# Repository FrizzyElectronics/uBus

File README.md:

# uBus
Conversor USB-micro a Serial IC. 5V/3.3V compatible

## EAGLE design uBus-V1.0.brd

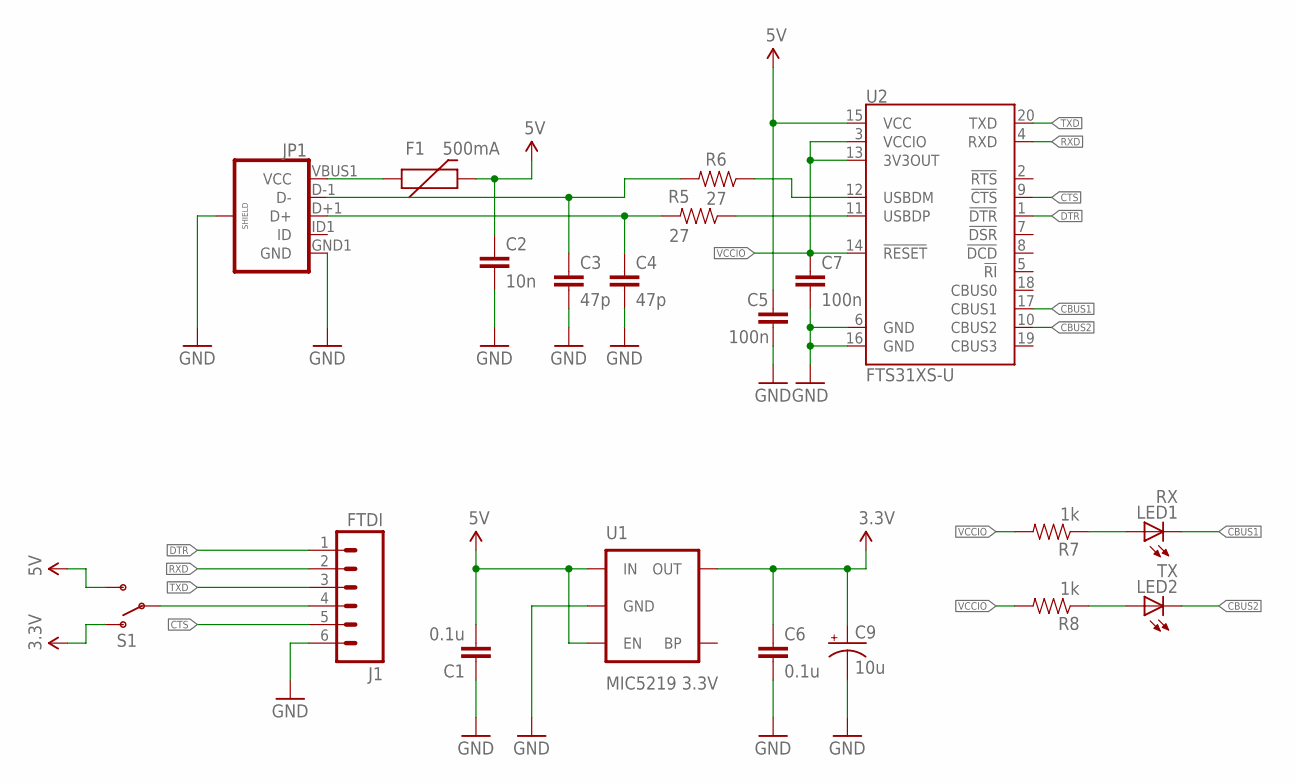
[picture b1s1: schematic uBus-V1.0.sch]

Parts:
C1, C6: 0.1u; 0603-CAP
C2: 10n; 0603-CAP
C3, C4: 47p; 0603-CAP
C5, C7: 100n; 0603-CAP
C9: 10u; SMC_P
F1: 500mA; PTC-1206
J1: FTDI; 1X06_LONGPADS
JP1: USB_MICROB_PLUGCONN-11752; USB-B-MICRO-SMD_V03
LED1: RX; CHIP-LED0603
LED2: TX; CHIP-LED0603
R5, R6: 27; 0603-RES
R7, R8: 1k; 0603-RES
S1: SWITCH-SPDT-SMD-A; SWITCH-SPST-SMD-A
U1: MIC5219 3.3V; SOT23-5
U2: FTS31XS-U; SSOP20_L

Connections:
3.3V: C6.1, C9.+, S1.1 (O), U1.5 (OUT)
5V: C1.2, C2.1, C5.1, F1.2, S1.3 (S), U1.1 (IN), U1.3 (EN), U2.15 (VCC)
CBUS1: LED1.C, U2.17 (CBUS1)
CBUS2: LED2.C, U2.10 (CBUS2)
CTS: J1.5, U2.9 (!CTS)
DTR: J1.1, U2.1 (!DTR)
GND: C1.1, C2.2, C3.2, C4.2, C5.2, C6.2, C7.2, C9.-, J1.6, JP1.GND1 (GND), JP1.SHIELD1 (SHIELD), JP1.SHIELD2 (SHIELD), JP1.SHIELD3 (SHIELD), U1.2 (GND), U2.6 (GND), U2.16 (GND)
unnamed: J1.4, S1.2
unnamed: LED2.A, R8.1
unnamed: LED1.A, R7.1
unnamed: R6.1, U2.12 (USBDM)
unnamed: R5.1, U2.11 (USBDP)
unnamed: C4.1, JP1.D+1 (D+), R5.2
unnamed: C3.1, JP1.D-1 (D-), R6.2
unnamed: F1.1, JP1.VBUS1 (VCC)
RXD: J1.2, U2.4 (RXD)
TXD: J1.3, U2.20 (TXD)
VCCIO: C7.1, R7.2, R8.2, U2.3 (VCCIO), U2.13 (3V3OUT), U2.14 (!RESET)

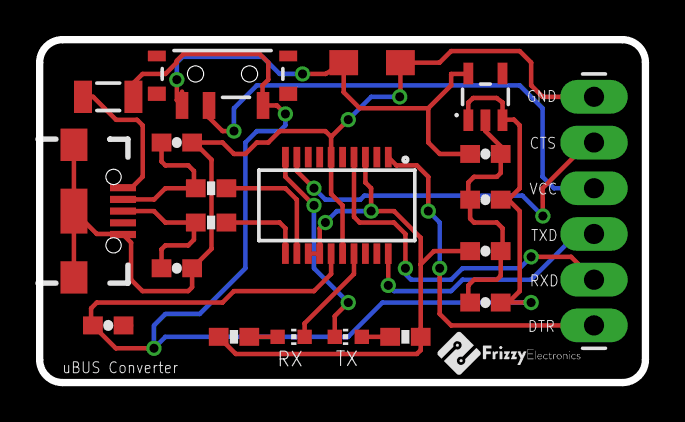
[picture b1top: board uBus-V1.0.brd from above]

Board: 2 copper layers, 33.7 x 19.0 mm, 21 parts (1 on the bottom side), 18 nets.

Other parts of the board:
U$1: OSHW-LOGO-S

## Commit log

2016-07-25 Update License.md
    Update License.md
2016-07-25 Esquematico actualizado
2016-07-31 Conversor USB-micro a Serial IC. 5V/3.3V compatible
    Enrrutado terminado
2016-08-03 Placa mandada a fabrica
    Logos añadidos
2016-11-19 Errores corregidos

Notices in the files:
parts and their libraries:
SparkFun-Passives: Licensing: Creative Commons ShareAlike 4.0 International - https://creativecommons.org/licenses/by-sa/4.0
